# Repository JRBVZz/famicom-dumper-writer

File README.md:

### Famicom Dumper - дампер/программатор для картриджей Famicom/Dendy

Цель проекта — создание идеального симулятора шины данных Famicom. Он использует очень точную симуляцию цикла M2 и FSMC для доступа к памяти PRG и CHR. Кроме того, этот дампер имеет высокую скорость чтения/записи больших многоигровок.  
  
Главные отличия данного форка от оригинального проекта: полностью изменена трассировка; выводные светодиоды заменены на SMD; есть возможность установки на выбор THT или SMD версии кварцевого резонатора; убран разъем NES.  
  
В папке **STM32-Dumper** находится KiCad проект и гербер файлы для производства.  

Проект создан в [**KiCad 9**](https://www.kicad.org/).

### Сборка

#### BoM и Schematic
[BoM](Dumper-Docs/Dumper-BOM.jpg)  
  
[Schematic](Dumper-Docs/STM32-Dumper-Schematic.pdf)

Выберите какой кварцевый резонатор ставить - SMD **Y1**, или THT **Y2**.  
Вместо шифтера **U7** можно установить два резистора **R11, R12**.  

#### Firmware
В папке **Dumper-Firmware** находятся файлы для прошивки STM32 и EPM3064:  
**FamicomDumper.pof** - файл для прошивки EPM3064 с помощью USB-Blaster. Исходники находятся в архиве Dumper-CPLD.zip  
**FamicomDumperBootloader.bin** - бутлоадер для STM32, для прошивки можно использовать программу STM32 ST-LINK Utility и дешёвый донгл ST-LINK. Вручную укажите адрес для записи **0x08000000**.  
**FamicomDumper.bin** - основная программа для STM32. Вручную укажите адрес для записи **0x08040000**.  

### Software

[https://github.com/ClusterM/famicom-dumper-client](https://github.com/ClusterM/famicom-dumper-client)

#### P.S.

Мне не очень нравится идея преобразования сигналов до уровня 5В. Да, для старых картриджей это нормально, но современные дешевые многоигровки используют чипы с питанием 3.3В и в подавляющем большинстве случаев не имеют преобразователей уровней. Поэтому 5В сигналы для них, мягко говоря, не полезны. Как вариант, использовать 74LVC245A вместо 74LVC8T245.

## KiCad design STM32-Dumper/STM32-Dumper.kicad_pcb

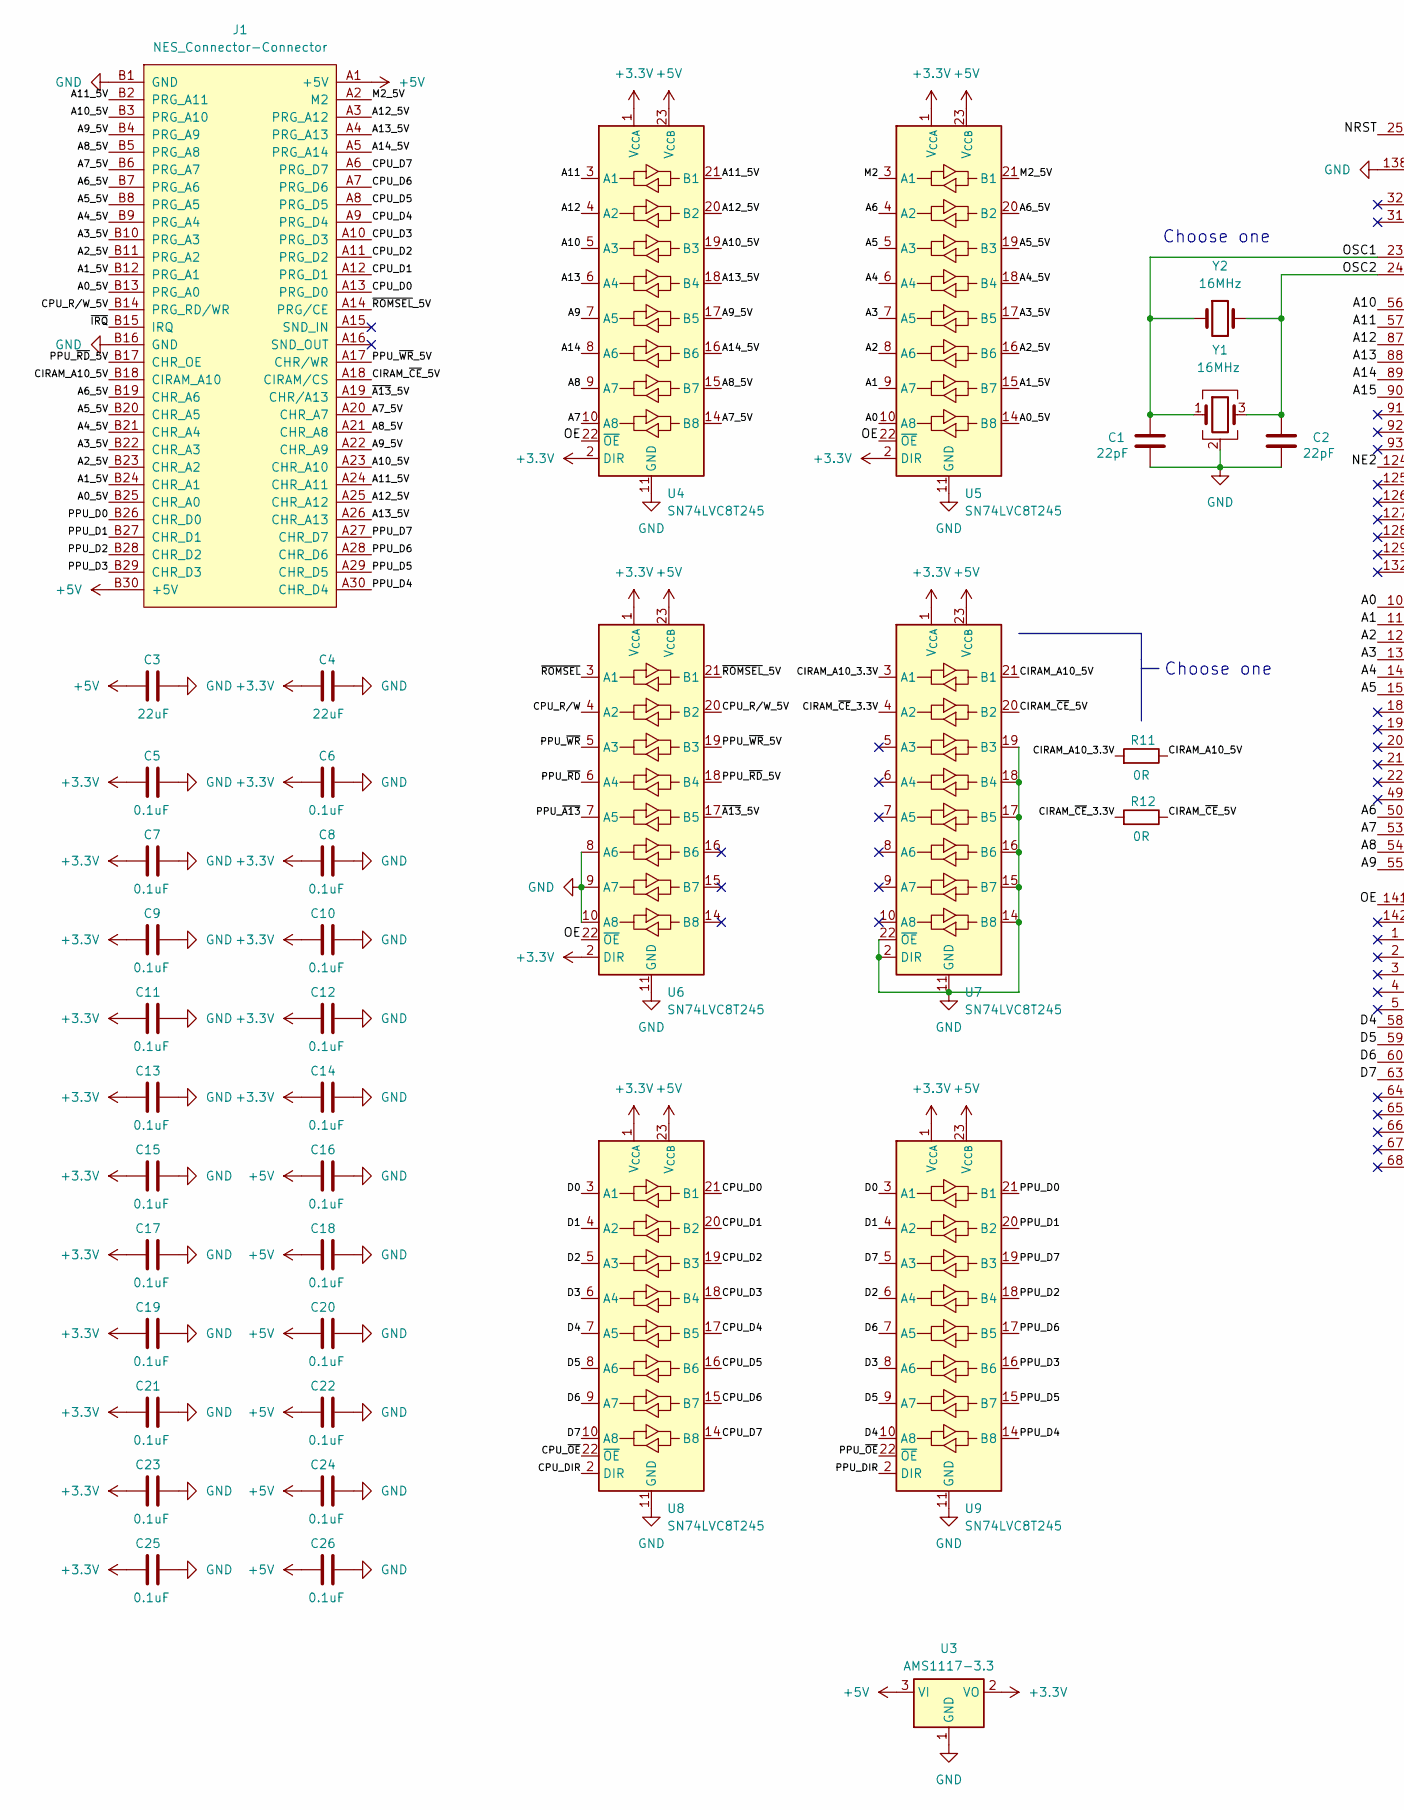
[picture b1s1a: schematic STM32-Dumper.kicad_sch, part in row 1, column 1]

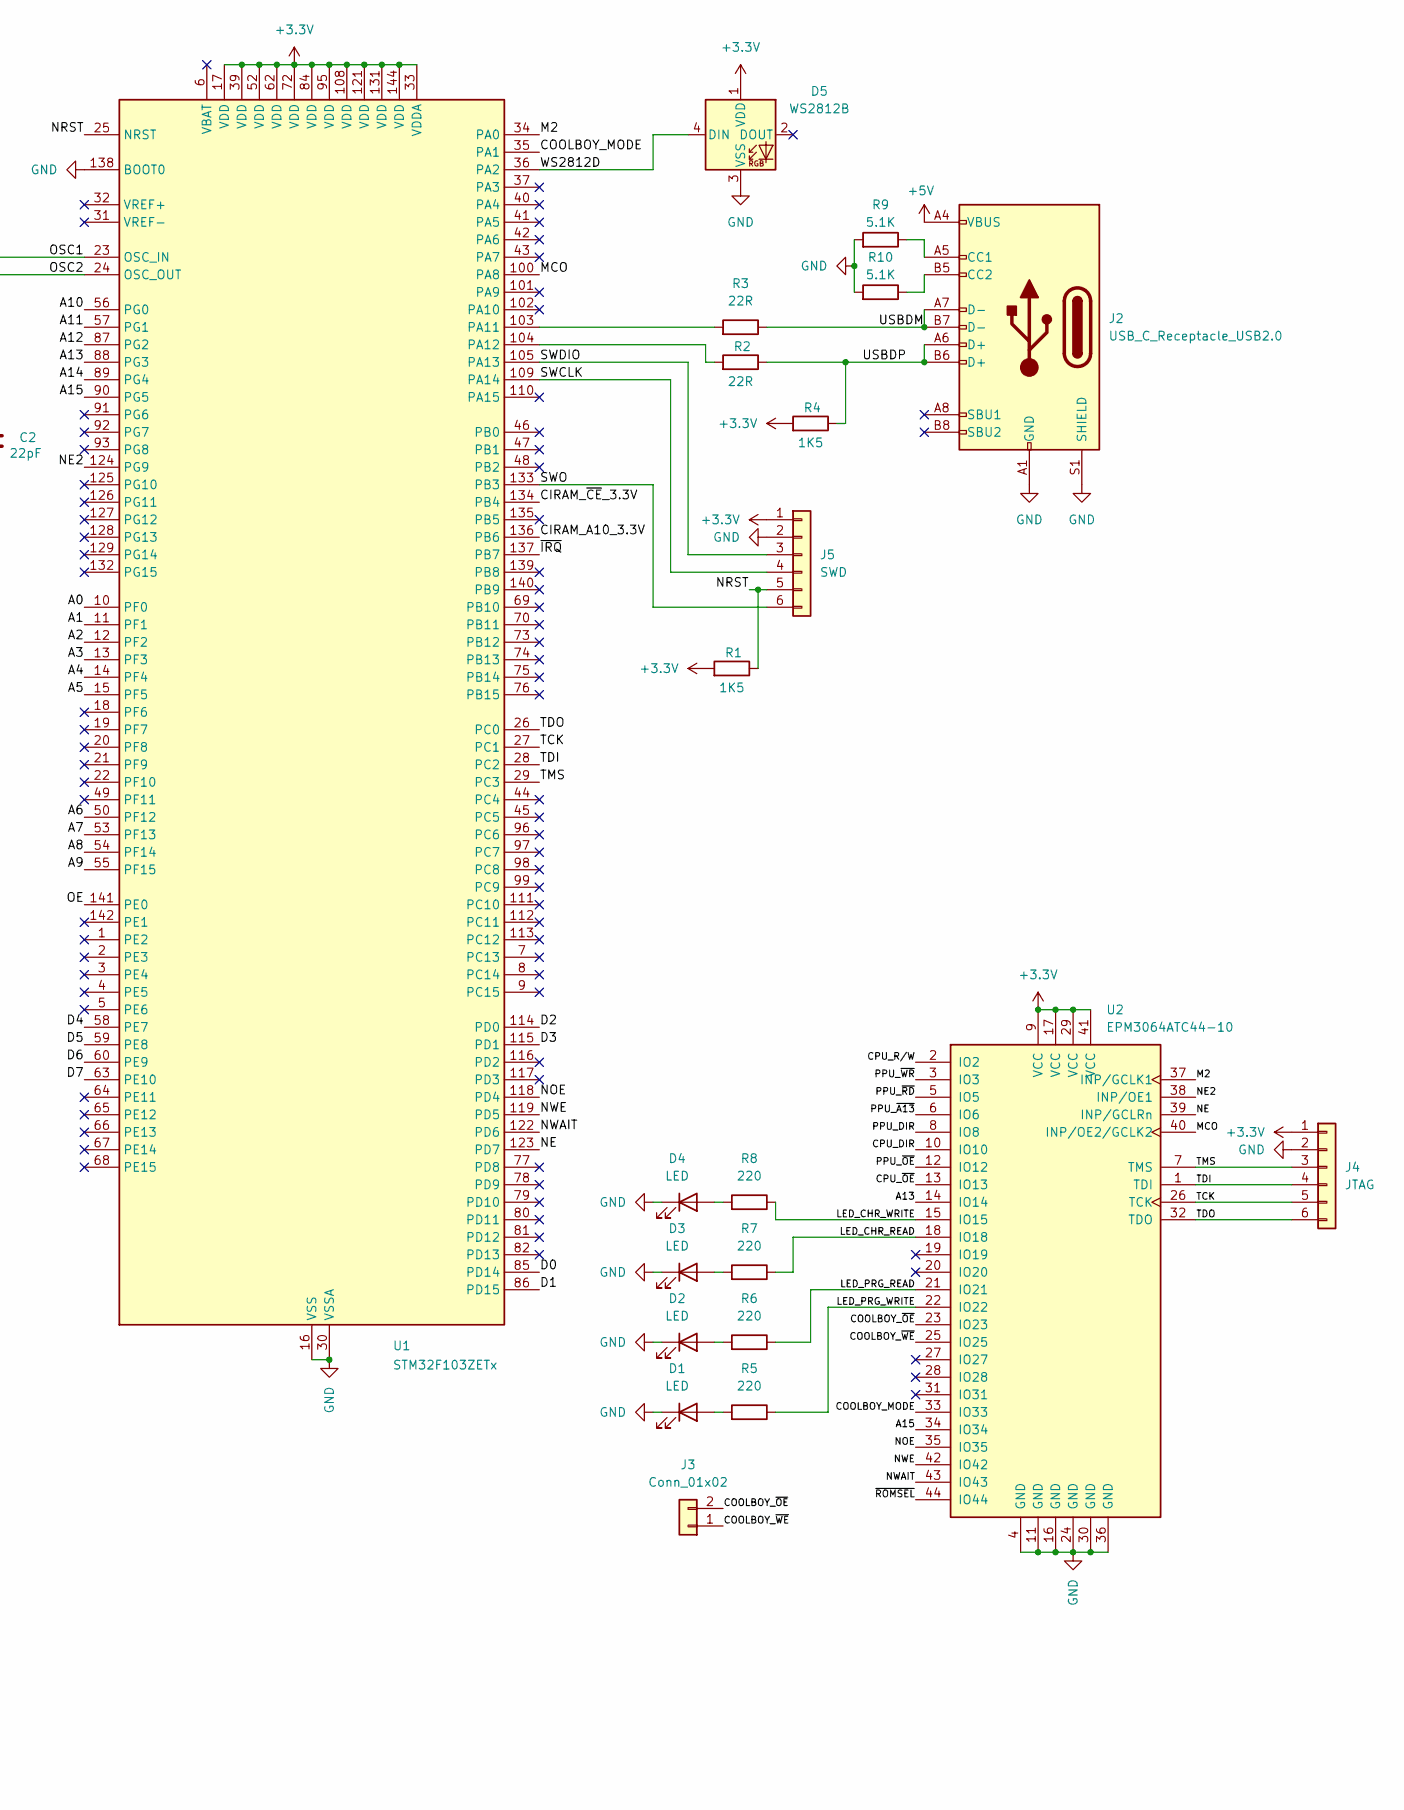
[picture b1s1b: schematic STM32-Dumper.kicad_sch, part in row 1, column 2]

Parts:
C1, C2: 22pF; C_0805_2012Metric
C3, C4: 22uF; C_0805_2012Metric
C5, C6, C7, C8, C9, C10, C11, C12, C13, C14, C15, C16, C17, C18, C19, C20, C21, C22, C23, C24, C25, C26: 0.1uF; C_0603_1608Metric_Pad1.08x0.95mm_HandSolder
D1, D2, D3, D4: LED; LED_0805_2012Metric
D5: WS2812B; LED_WS2812B_PLCC4_5.0x5.0mm_P3.2mm
J1: NES_Connector-Connector; Dendy_Socket
J2: USB_C_Receptacle_USB2.0; USB_C_Receptacle_Palconn_UTC16-G
J3: Conn_01x02; PinHeader_1x02_P2.54mm_Vertical
J4: JTAG; PinHeader_1x06_P2.54mm_Vertical
J5: SWD; PinHeader_1x06_P2.54mm_Vertical
R1, R4: 1K5; R_0805_2012Metric
R2, R3: 22R; R_0805_2012Metric
R5, R6, R7, R8: 220; R_0805_2012Metric
R9, R10: 5.1K; R_0805_2012Metric
R11, R12: 0R; R_0402_1005Metric_Pad0.72x0.64mm_HandSolder
U1: STM32F103ZETx; LQFP-144_20x20mm_P0.5mm
U2: EPM3064ATC44-10; TQFP-44_10x10mm_P0.8mm
U3: AMS1117-3.3; SOT-223-3_TabPin2
U4, U5, U6, U7, U8, U9: SN74LVC8T245; TSSOP-24_4.4x7.8mm_P0.65mm
Y1: 16MHz; Crystal_SMD_3225-4Pin_3.2x2.5mm
Y2: 16MHz; Crystal_HC49-4H_Vertical

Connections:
+3.3V: C4.1, C5.1, C6.1, C7.1, C8.1, C9.1, C10.1, C11.1, C12.1, C13.1, C14.1, C15.1, C17.1, C19.1, C21.1, C23.1, C25.1, D5.1 (VDD), J4.1, J5.1, R1.2, R4.2, U1.17 (VDD), U1.33 (VDDA), U1.39 (VDD), U1.52 (VDD), U1.62 (VDD), U1.72 (VDD), U1.84 (VDD), U1.95 (VDD), U1.108 (VDD), U1.121 (VDD), U1.131 (VDD), U1.144 (VDD), U2.9 (VCC), U2.17 (VCC), U2.29 (VCC), U2.41 (VCC), U3.2 (VO), U4.1 (V_{CCA}), U4.2 (DIR), U5.1 (V_{CCA}), U5.2 (DIR), U6.1 (V_{CCA}), U6.2 (DIR), U7.1 (V_{CCA}), U8.1 (V_{CCA}), U9.1 (V_{CCA})
+5V: C3.1, C16.1, C18.1, C20.1, C22.1, C24.1, C26.1, J1.A1 (+5V), J1.B30 (+5V), J2.A4 (VBUS), J2.A9 (VBUS), J2.B4 (VBUS), J2.B9 (VBUS), U3.3 (VI), U4.23 (V_{CCB}), U4.24 (V_{CCB}), U5.23 (V_{CCB}), U5.24 (V_{CCB}), U6.23 (V_{CCB}), U6.24 (V_{CCB}), U7.23 (V_{CCB}), U7.24 (V_{CCB}), U8.23 (V_{CCB}), U8.24 (V_{CCB}), U9.23 (V_{CCB}), U9.24 (V_{CCB})
/A0: U1.10 (PF0), U5.10 (A8)
/A0_5V: J1.B13 (PRG_A0), J1.B25 (CHR_A0), U5.14 (B8)
/A1: U1.11 (PF1), U5.9 (A7)
/A1_5V: J1.B12 (PRG_A1), J1.B24 (CHR_A1), U5.15 (B7)
/A2: U1.12 (PF2), U5.8 (A6)
/A2_5V: J1.B11 (PRG_A2), J1.B23 (CHR_A2), U5.16 (B6)
/A3: U1.13 (PF3), U5.7 (A5)
/A3_5V: J1.B10 (PRG_A3), J1.B22 (CHR_A3), U5.17 (B5)
/A4: U1.14 (PF4), U5.6 (A4)
/A4_5V: J1.B9 (PRG_A4), J1.B21 (CHR_A4), U5.18 (B4)
/A5: U1.15 (PF5), U5.5 (A3)
/A5_5V: J1.B8 (PRG_A5), J1.B20 (CHR_A5), U5.19 (B3)
/A6: U1.50 (PF12), U5.4 (A2)
/A6_5V: J1.B7 (PRG_A6), J1.B19 (CHR_A6), U5.20 (B2)
/A7: U1.53 (PF13), U4.10 (A8)
/A7_5V: J1.A20 (CHR_A7), J1.B6 (PRG_A7), U4.14 (B8)
/A8: U1.54 (PF14), U4.9 (A7)
/A8_5V: J1.A21 (CHR_A8), J1.B5 (PRG_A8), U4.15 (B7)
/A9: U1.55 (PF15), U4.7 (A5)
/A9_5V: J1.A22 (CHR_A9), J1.B4 (PRG_A9), U4.17 (B5)
/A10: U1.56 (PG0), U4.5 (A3)
/A10_5V: J1.A23 (CHR_A10), J1.B3 (PRG_A10), U4.19 (B3)
/A11: U1.57 (PG1), U4.3 (A1)
/A11_5V: J1.A24 (CHR_A11), J1.B2 (PRG_A11), U4.21 (B1)
/A12: U1.87 (PG2), U4.4 (A2)
/A12_5V: J1.A3 (PRG_A12), J1.A25 (CHR_A12), U4.20 (B2)
/A13: U1.88 (PG3), U2.14 (IO14), U4.6 (A4)
/A13_5V: J1.A4 (PRG_A13), J1.A26 (CHR_A13), U4.18 (B4)
/A14: U1.89 (PG4), U4.8 (A6)
/A14_5V: J1.A5 (PRG_A14), U4.16 (B6)
/A15: U1.90 (PG5), U2.34 (IO34)
/CIRAM_A10_3.3V: R11.2, U1.136 (PB6), U7.3 (A1)
/CIRAM_A10_5V: J1.B18 (CIRAM_A10), R11.1, U7.21 (B1)
/CIRAM_~CE_3.3V: R12.2, U1.134 (PB4), U7.4 (A2)
/CIRAM_~CE_5V: J1.A18 (CIRAM/CS), R12.1, U7.20 (B2)
/COOLBOY_MODE: U1.35 (PA1), U2.33 (IO33)
/COOLBOY_~OE: J3.2, U2.23 (IO23)
/COOLBOY_~WE: J3.1, U2.25 (IO25)
/CPU_D0: J1.A13 (PRG_D0), U8.21 (B1)
/CPU_D1: J1.A12 (PRG_D1), U8.20 (B2)
/CPU_D2: J1.A11 (PRG_D2), U8.19 (B3)
/CPU_D3: J1.A10 (PRG_D3), U8.18 (B4)
/CPU_D4: J1.A9 (PRG_D4), U8.17 (B5)
/CPU_D5: J1.A8 (PRG_D5), U8.16 (B6)
/CPU_D6: J1.A7 (PRG_D6), U8.15 (B7)
/CPU_D7: J1.A6 (PRG_D7), U8.14 (B8)
/CPU_DIR: U2.10 (IO10), U8.2 (DIR)
/CPU_R/W: U2.2 (IO2), U6.4 (A2)
/CPU_R/W_5V: J1.B14 (PRG_RD/WR), U6.20 (B2)
/CPU_~OE: U2.13 (IO13), U8.22 (~OE)
/D0: U1.85 (PD14), U8.3 (A1), U9.3 (A1)
/D1: U1.86 (PD15), U8.4 (A2), U9.4 (A2)
/D2: U1.114 (PD0), U8.5 (A3), U9.6 (A4)
/D3: U1.115 (PD1), U8.6 (A4), U9.8 (A6)
/D4: U1.58 (PE7), U8.7 (A5), U9.10 (A8)
/D5: U1.59 (PE8), U8.8 (A6), U9.9 (A7)
/D6: U1.60 (PE9), U8.9 (A7), U9.7 (A5)
/D7: U1.63 (PE10), U8.10 (A8), U9.5 (A3)
/LED_CHR_READ: R7.1, U2.18 (IO18)
/LED_CHR_WRITE: R8.1, U2.15 (IO15)
/LED_PRG_READ: R6.1, U2.21 (IO21)
/LED_PRG_WRITE: R5.1, U2.22 (IO22)
/M2: U1.34 (PA0), U2.37 (INP/GCLK1), U5.3 (A1)
/M2_5V: J1.A2 (M2), U5.21 (B1)
/MCO: U1.100 (PA8), U2.40 (INP/OE2/GCLK2)
/NE: U1.123 (PD7), U2.39 (INP/GCLRn)
/NE2: U1.124 (PG9), U2.38 (INP/OE1)
/NOE: U1.118 (PD4), U2.35 (IO35)
/NRST: J5.5, R1.1, U1.25 (NRST)
/NWAIT: U1.122 (PD6), U2.43 (IO43)
/NWE: U1.119 (PD5), U2.42 (IO42)
/OE: U1.141 (PE0), U4.22 (~OE), U5.22 (~OE), U6.22 (~OE)
/OSC1: C1.2, U1.23 (OSC_IN), Y1.1, Y2.1
/OSC2: C2.2, U1.24 (OSC_OUT), Y1.3, Y2.2
/PPU_D0: J1.B26 (CHR_D0), U9.21 (B1)
/PPU_D1: J1.B27 (CHR_D1), U9.20 (B2)
/PPU_D2: J1.B28 (CHR_D2), U9.18 (B4)
/PPU_D3: J1.B29 (CHR_D3), U9.16 (B6)
/PPU_D4: J1.A30 (CHR_D4), U9.14 (B8)
/PPU_D5: J1.A29 (CHR_D5), U9.15 (B7)
/PPU_D6: J1.A28 (CHR_D6), U9.17 (B5)
/PPU_D7: J1.A27 (CHR_D7), U9.19 (B3)
/PPU_DIR: U2.8 (IO8), U9.2 (DIR)
/PPU_~A13: U2.6 (IO6), U6.7 (A5)
/PPU_~OE: U2.12 (IO12), U9.22 (~OE)
/PPU_~RD: U2.5 (IO5), U6.6 (A4)
/PPU_~RD_5V: J1.B17 (CHR_OE), U6.18 (B4)
/PPU_~WR: U2.3 (IO3), U6.5 (A3)
/PPU_~WR_5V: J1.A17 (CHR/WR), U6.19 (B3)
/SWCLK: J5.4, U1.109 (PA14)
/SWDIO: J5.3, U1.105 (PA13)
/SWO: J5.6, U1.133 (PB3)
/TCK: J4.5, U1.27 (PC1), U2.26 (TCK)
/TDI: J4.4, U1.28 (PC2), U2.1 (TDI)
/TDO: J4.6, U1.26 (PC0), U2.32 (TDO)
/TMS: J4.3, U1.29 (PC3), U2.7 (TMS)
/USBDM: J2.A7 (D-), J2.B7 (D-), R3.1
/USBDP: J2.A6 (D+), J2.B6 (D+), R2.1, R4.1
/WS2812D: D5.4 (DIN), U1.36 (PA2)
/~A13_5V: J1.A19 (CHR/A13), U6.17 (B5)
/~IRQ: J1.B15 (IRQ), U1.137 (PB7)
/~ROMSEL: U2.44 (IO44), U6.3 (A1)
/~ROMSEL_5V: J1.A14 (PRG/CE), U6.21 (B1)
GND: C1.1, C2.1, C3.2, C4.2, C5.2, C6.2, C7.2, C8.2, C9.2, C10.2, C11.2, C12.2, C13.2, C14.2, C15.2, C16.2, C17.2, C18.2, C19.2, C20.2, C21.2, C22.2, C23.2, C24.2, C25.2, C26.2, D1.1 (K), D2.1 (K), D3.1 (K), D4.1 (K), D5.3 (VSS), J1.B1 (GND), J1.B16 (GND), J2.A1 (GND), J2.A12 (GND), J2.B1 (GND), J2.B12 (GND), J2.S1 (SHIELD), J4.2, J5.2, R9.2, R10.2, U1.16 (VSS), U1.30 (VSSA), U1.38 (VSS), U1.51 (VSS), U1.61 (VSS), U1.71 (VSS), U1.83 (VSS), U1.94 (VSS), U1.107 (VSS), U1.120 (VSS), U1.130 (VSS), U1.138 (BOOT0), U1.143 (VSS), U2.4 (GND), U2.11 (GND), U2.16 (GND), U2.24 (GND), U2.30 (GND), U2.36 (GND), U3.1 (GND), U4.11 (GND), U4.12 (GND), U4.13 (GND), U5.11 (GND), U5.12 (GND), U5.13 (GND), U6.8 (A6), U6.9 (A7), U6.10 (A8), U6.11 (GND), U6.12 (GND), U6.13 (GND), U7.2 (DIR), U7.11 (GND), U7.12 (GND), U7.13 (GND), U7.14 (B8), U7.15 (B7), U7.16 (B6), U7.17 (B5), U7.18 (B4), U7.19 (B3), U7.22 (~OE), U8.11 (GND), U8.12 (GND), U8.13 (GND), U9.11 (GND), U9.12 (GND), U9.13 (GND), Y1.2 (G), Y1.4 (G)
unnamed: D1.2 (A), R5.2
unnamed: D2.2 (A), R6.2
unnamed: D3.2 (A), R7.2
unnamed: D4.2 (A), R8.2
unnamed: J2.A5 (CC1), R9.1
unnamed: J2.B5 (CC2), R10.1
unnamed: R3.2, U1.103 (PA11)
unnamed: R2.2, U1.104 (PA12)

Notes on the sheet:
Choose one

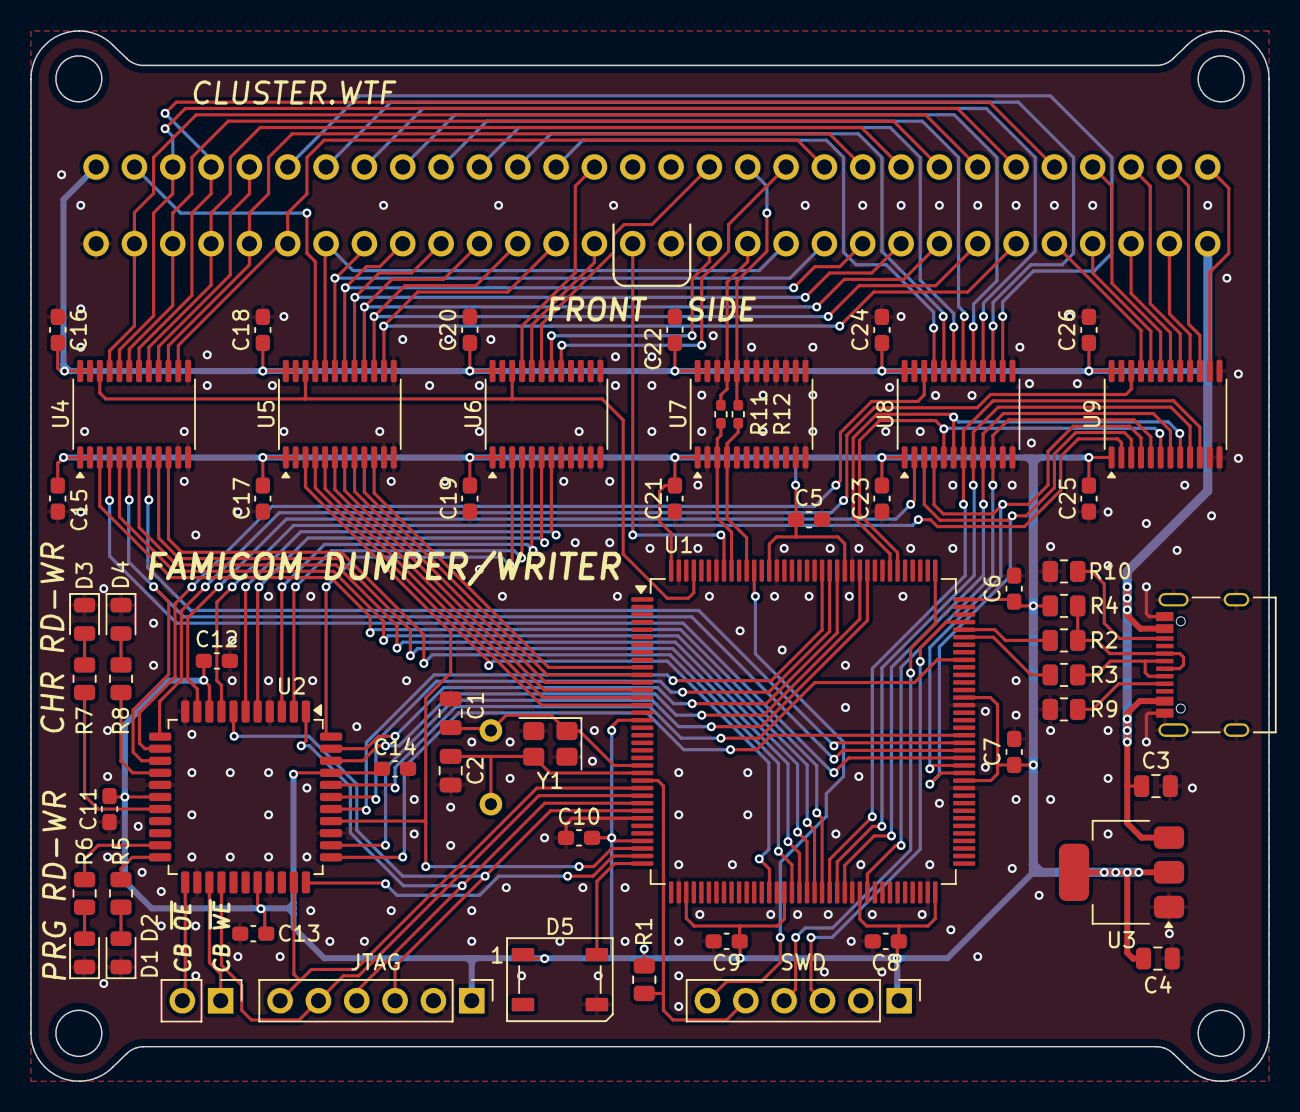
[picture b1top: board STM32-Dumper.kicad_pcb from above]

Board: 2 copper layers, 82.0 x 69.6 mm, 59 parts (1 on the bottom side), 114 nets.

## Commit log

2026-03-29 KiCad Project
